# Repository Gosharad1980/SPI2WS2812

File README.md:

# SPI 2 WS2812B
- Contrôler un strip de LED WS2812(B) en passant  via un bus SPI
- PCB et circuit issus du magazine ELEKTOR FRANCE

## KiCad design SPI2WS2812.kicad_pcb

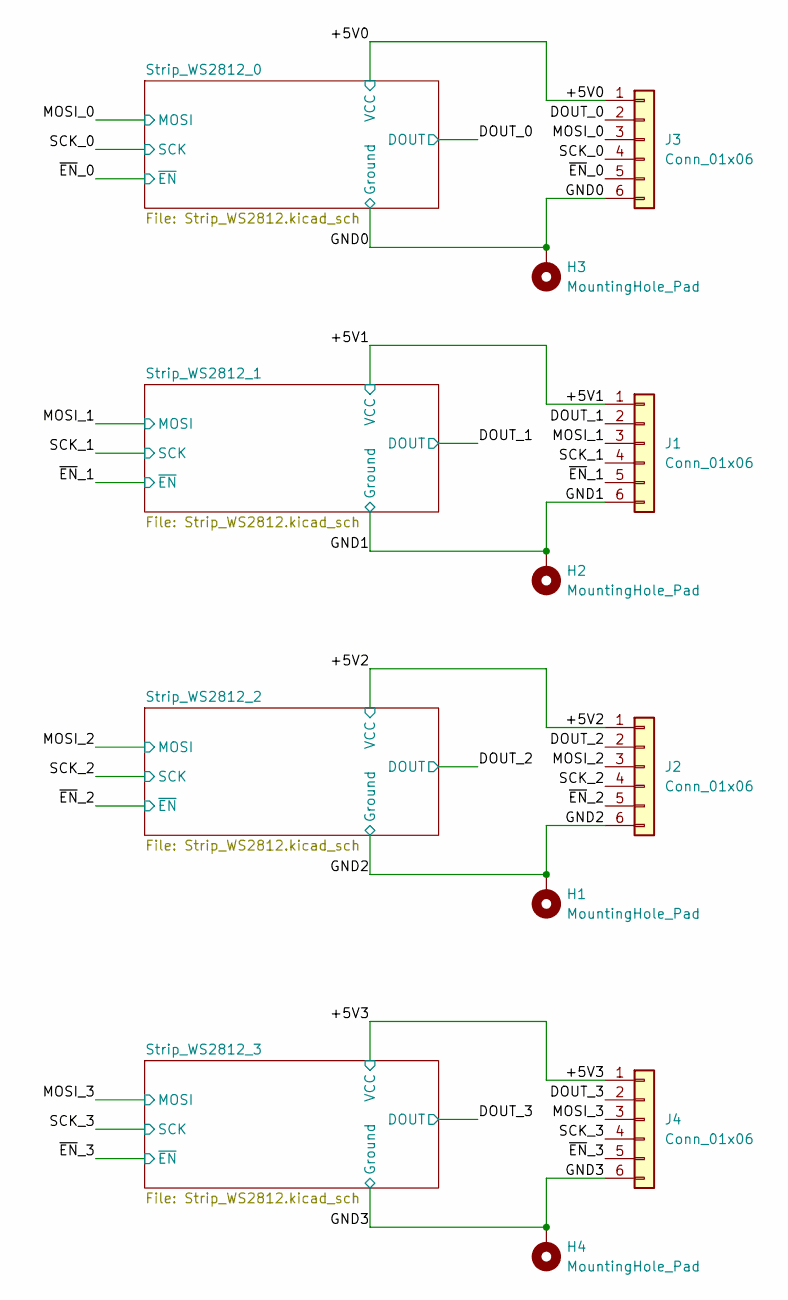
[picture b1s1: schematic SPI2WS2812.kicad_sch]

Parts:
H1, H2, H3, H4: MountingHole_Pad; MountingHole_3.2mm_M3_Pad_Via
J1, J2, J3, J4: Conn_01x06; PinHeader_1x06_P2.54mm_Vertical

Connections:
/+5V0: J3.1; also elsewhere on the board
/+5V1: J1.1; also elsewhere on the board
/+5V2: J2.1; also elsewhere on the board
/+5V3: J4.1; also elsewhere on the board
/DOUT_0: J3.2; also elsewhere on the board
/DOUT_1: J1.2; also elsewhere on the board
/DOUT_2: J2.2; also elsewhere on the board
/DOUT_3: J4.2; also elsewhere on the board
/GND0: H3.1, J3.6; also elsewhere on the board
/GND1: H2.1, J1.6; also elsewhere on the board
/GND2: H1.1, J2.6; also elsewhere on the board
/GND3: H4.1, J4.6; also elsewhere on the board
/MOSI_0: J3.3; also elsewhere on the board
/MOSI_1: J1.3; also elsewhere on the board
/MOSI_2: J2.3; also elsewhere on the board
/MOSI_3: J4.3; also elsewhere on the board
/SCK_0: J3.4; also elsewhere on the board
/SCK_1: J1.4; also elsewhere on the board
/SCK_2: J2.4; also elsewhere on the board
/SCK_3: J4.4; also elsewhere on the board
/~EN_0: J3.5; also elsewhere on the board
/~EN_1: J1.5; also elsewhere on the board
/~EN_2: J2.5; also elsewhere on the board
/~EN_3: J4.5; also elsewhere on the board

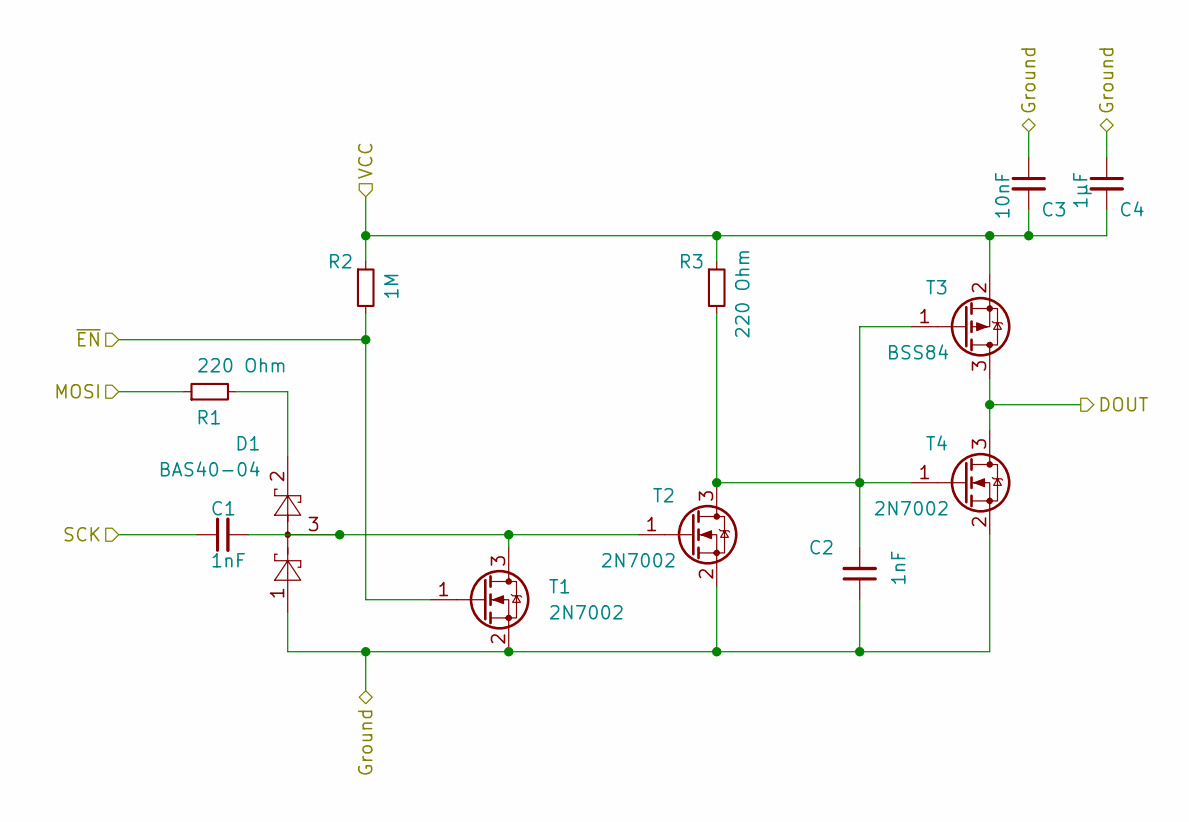
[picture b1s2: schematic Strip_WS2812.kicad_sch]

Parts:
C1, C2: 1nF; C_1210_3225Metric_Pad1.33x2.70mm_HandSolder
C3: 10nF; C_1210_3225Metric_Pad1.33x2.70mm_HandSolder
C4: 1µF; C_1210_3225Metric_Pad1.33x2.70mm_HandSolder
D1: BAS40-04; SOT-23
R1, R3: 220 Ohm; R_1210_3225Metric_Pad1.30x2.65mm_HandSolder
R2: 1M; R_1210_3225Metric_Pad1.30x2.65mm_HandSolder
T1, T2, T4: 2N7002; SOT-23_Handsoldering
T3: BSS84; SOT-23_Handsoldering

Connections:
/+5V0: C3.2, C4.2, R2.1, R3.1, T3.2 (S); also elsewhere on the board
/DOUT_0: T3.3 (D), T4.3 (D); also elsewhere on the board
/GND0: C2.1, C3.1, C4.1, D1.1, T1.2 (S), T2.2 (S), T4.2 (S); also elsewhere on the board
/MOSI_0: R1.1; also elsewhere on the board
/SCK_0: C1.1; also elsewhere on the board
/~EN_0: R2.2, T1.1 (G); also elsewhere on the board
unnamed: D1.2, R1.2
unnamed: C1.2, D1.3, T1.3 (D), T2.1 (G)
unnamed: C2.2, R3.2, T2.3 (D), T3.1 (G), T4.1 (G)

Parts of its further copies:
C5, C6, C9, C10, C13, C14: 1nF; C_1210_3225Metric_Pad1.33x2.70mm_HandSolder
C7, C11, C15: 10nF; C_1210_3225Metric_Pad1.33x2.70mm_HandSolder
C8, C12, C16: 1µF; C_1210_3225Metric_Pad1.33x2.70mm_HandSolder
D2, D3, D4: BAS40-04; SOT-23
R4, R6, R7, R9, R10, R12: 220 Ohm; R_1210_3225Metric_Pad1.30x2.65mm_HandSolder
R5, R8, R11: 1M; R_1210_3225Metric_Pad1.30x2.65mm_HandSolder
T5, T6, T8, T9, T10, T12, T13, T14, T16: 2N7002; SOT-23_Handsoldering
T7, T11, T15: BSS84; SOT-23_Handsoldering

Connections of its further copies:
/+5V1: C7.2, C8.2, R5.1, R6.1, T7.2 (S); also elsewhere on the board
/+5V2: C11.2, C12.2, R8.1, R9.1, T11.2 (S); also elsewhere on the board
/+5V3: C15.2, C16.2, R11.1, R12.1, T15.2 (S); also elsewhere on the board
/DOUT_1: T7.3 (D), T8.3 (D); also elsewhere on the board
/DOUT_2: T11.3 (D), T12.3 (D); also elsewhere on the board
/DOUT_3: T15.3 (D), T16.3 (D); also elsewhere on the board
/GND1: C6.1, C7.1, C8.1, D2.1, T5.2 (S), T6.2 (S), T8.2 (S); also elsewhere on the board
/GND2: C10.1, C11.1, C12.1, D3.1, T9.2 (S), T10.2 (S), T12.2 (S); also elsewhere on the board
/GND3: C14.1, C15.1, C16.1, D4.1, T13.2 (S), T14.2 (S), T16.2 (S); also elsewhere on the board
/MOSI_1: R4.1; also elsewhere on the board
/MOSI_2: R7.1; also elsewhere on the board
/MOSI_3: R10.1; also elsewhere on the board
/SCK_1: C5.1; also elsewhere on the board
/SCK_2: C9.1; also elsewhere on the board
/SCK_3: C13.1; also elsewhere on the board
/~EN_1: R5.2, T5.1 (G); also elsewhere on the board
/~EN_2: R8.2, T9.1 (G); also elsewhere on the board
/~EN_3: R11.2, T13.1 (G); also elsewhere on the board
unnamed: D2.2, R4.2
unnamed: D3.2, R7.2
unnamed: D4.2, R10.2
unnamed: C5.2, D2.3, T5.3 (D), T6.1 (G)
unnamed: C6.2, R6.2, T6.3 (D), T7.1 (G), T8.1 (G)
unnamed: C10.2, R9.2, T10.3 (D), T11.1 (G), T12.1 (G)
unnamed: C9.2, D3.3, T9.3 (D), T10.1 (G)
unnamed: C13.2, D4.3, T13.3 (D), T14.1 (G)
unnamed: C14.2, R12.2, T14.3 (D), T15.1 (G), T16.1 (G)

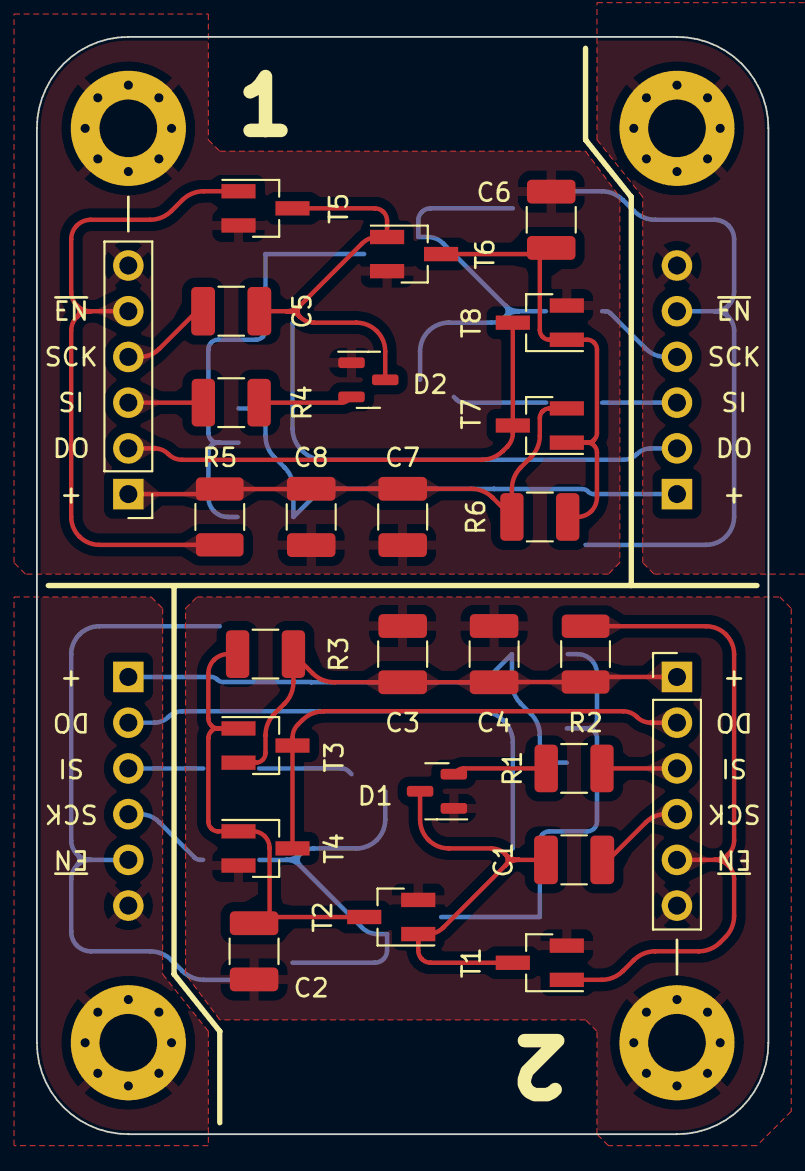
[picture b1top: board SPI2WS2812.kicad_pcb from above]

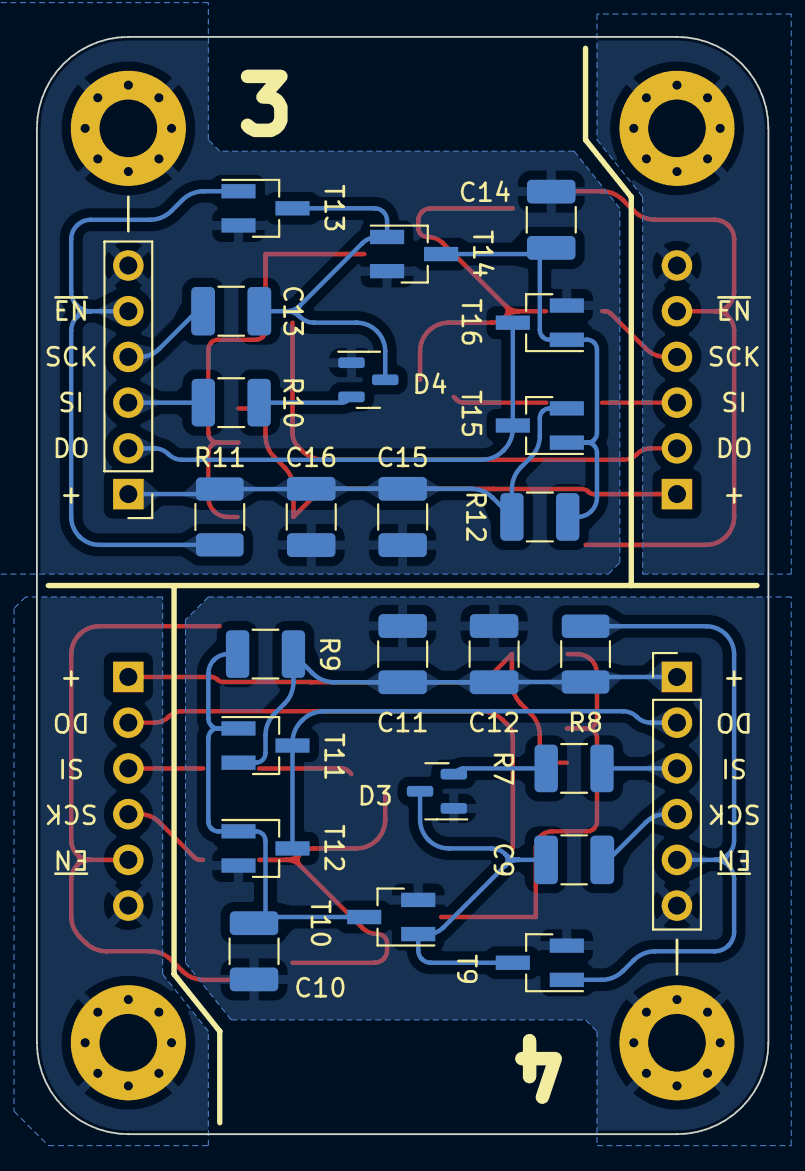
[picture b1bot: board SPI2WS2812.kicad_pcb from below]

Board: 2 copper layers, 40.6 x 61.0 mm, 56 parts (26 on the bottom side), 36 nets.

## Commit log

2022-10-30 Imported folder structure
2022-10-30 Premier commit :)
2022-11-27 Bon pour fabrication. Il ne reste plus qu'à faire une release v1.0
2022-11-27 Allez on ajoute les ref des pins de chaque côté du PCB -> régénération des fichiers de fabrication
2022-12-02 Avec les réglages "Rancunes"
2022-12-04 Allez on arrondi les angles
2023-02-20 KiCad 7.0
2023-03-27 KiCad 7.0 Tentative de modélisation Spice
2023-04-01 On ajoute en interne le projet de simulation Spice sous KiCad de la brique de base de la carte.
2023-04-02 Création du Gerber avec les pistes arrondies.
2023-05-23 Ajout des teardrops
2024-08-24 Kicad 8.0 et cosmétique
2025-02-19 Nettoyage du répertoires des trucs inutiles
2025-02-19 Suppression des fichiers surnuméraires
2025-02-19 Ajout d'un README
